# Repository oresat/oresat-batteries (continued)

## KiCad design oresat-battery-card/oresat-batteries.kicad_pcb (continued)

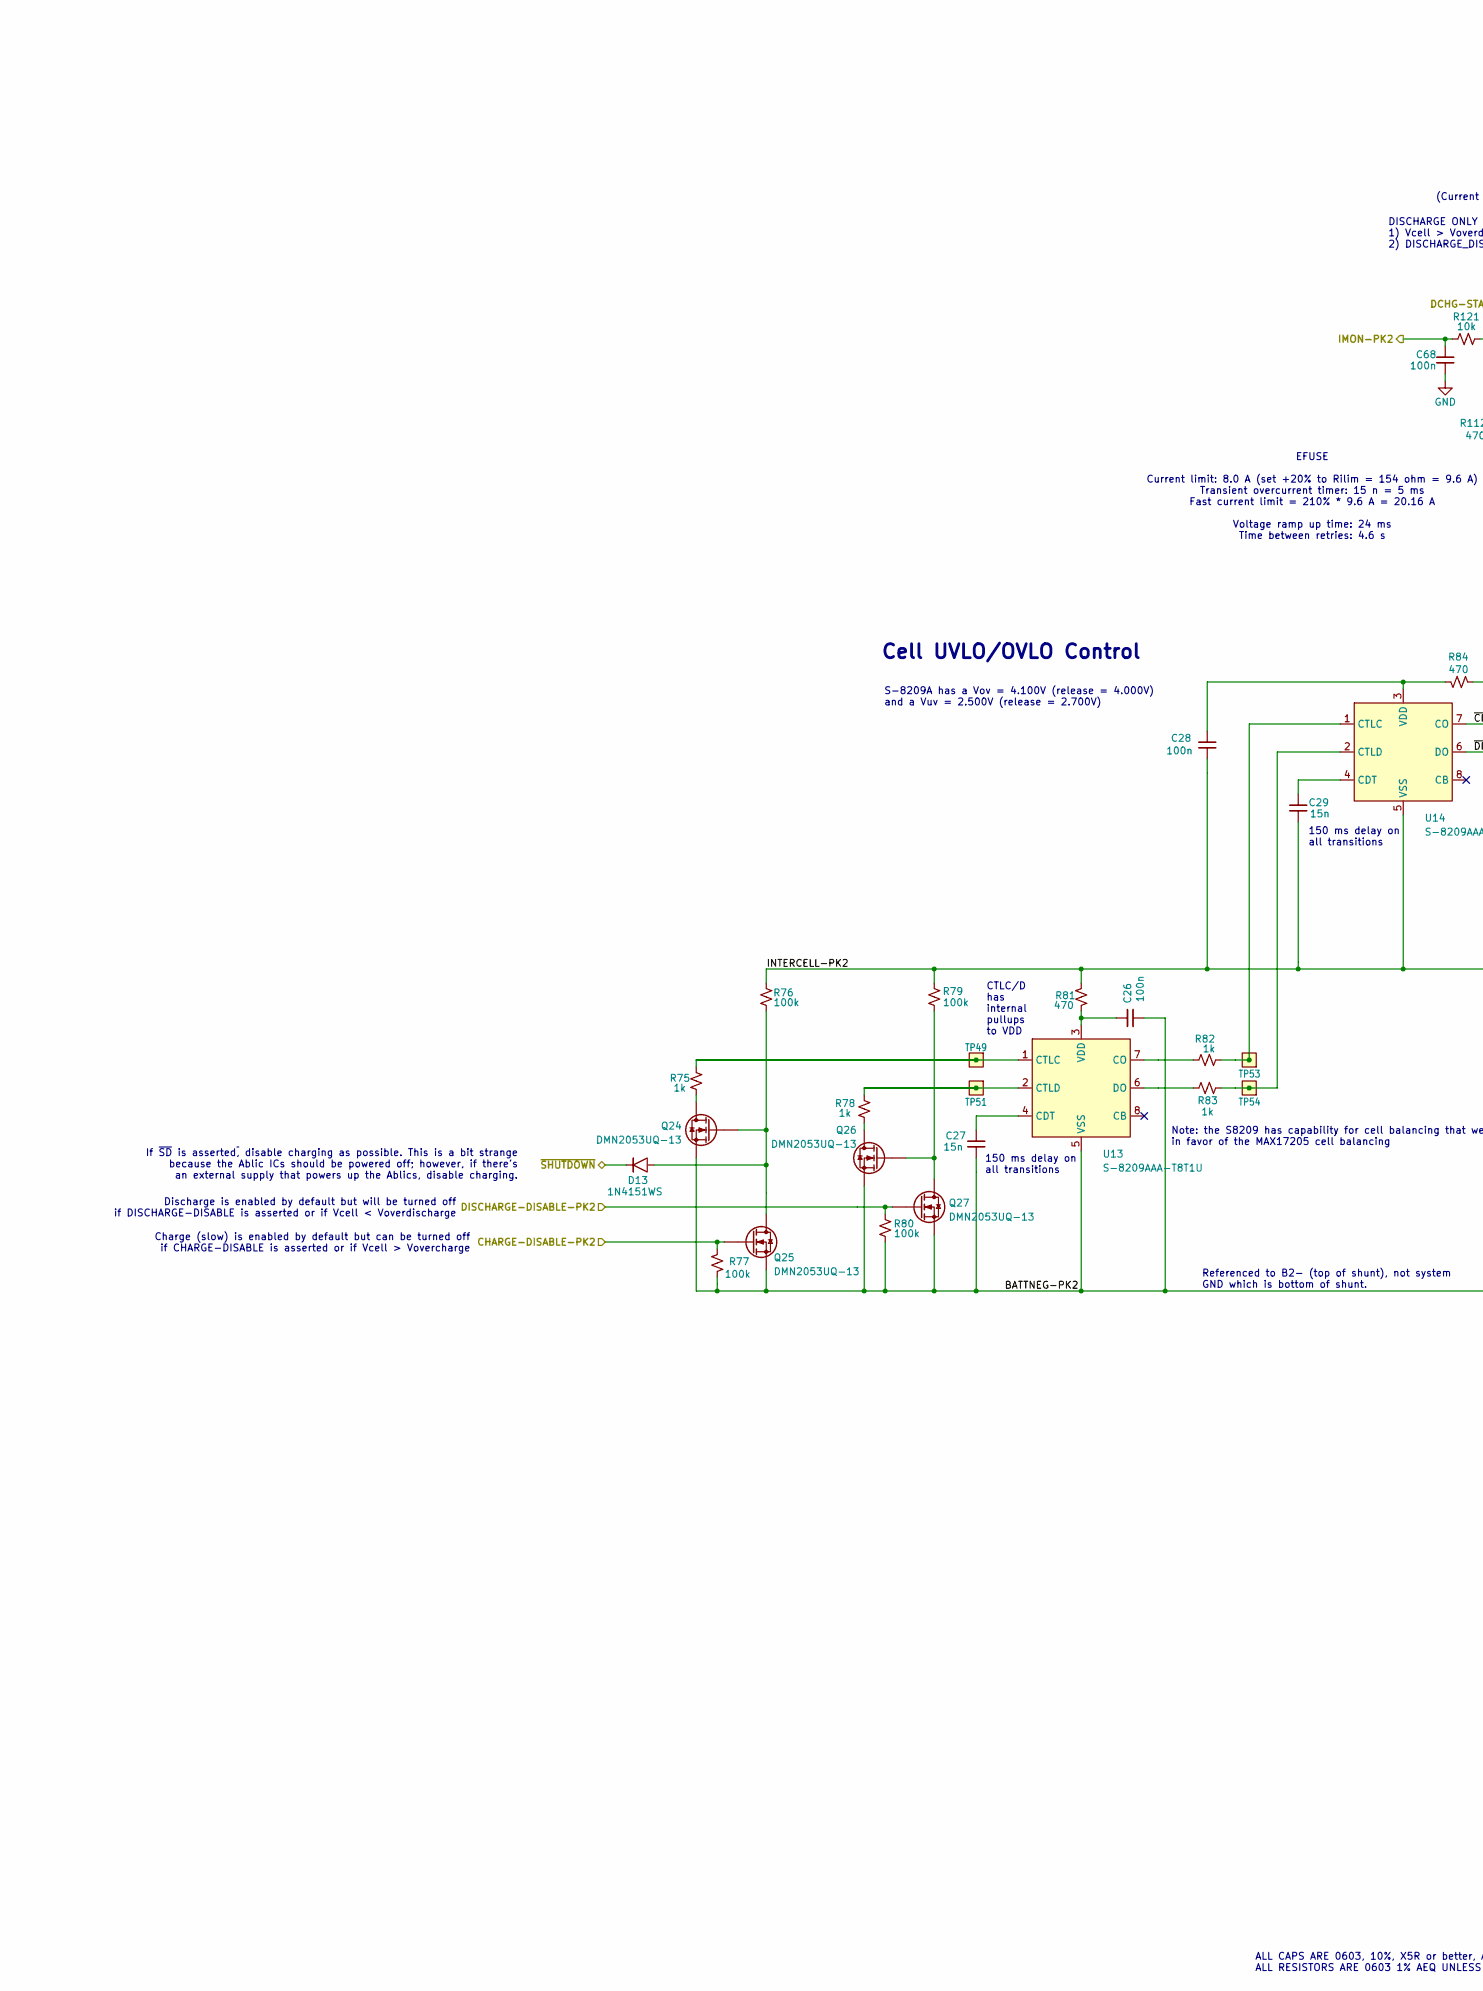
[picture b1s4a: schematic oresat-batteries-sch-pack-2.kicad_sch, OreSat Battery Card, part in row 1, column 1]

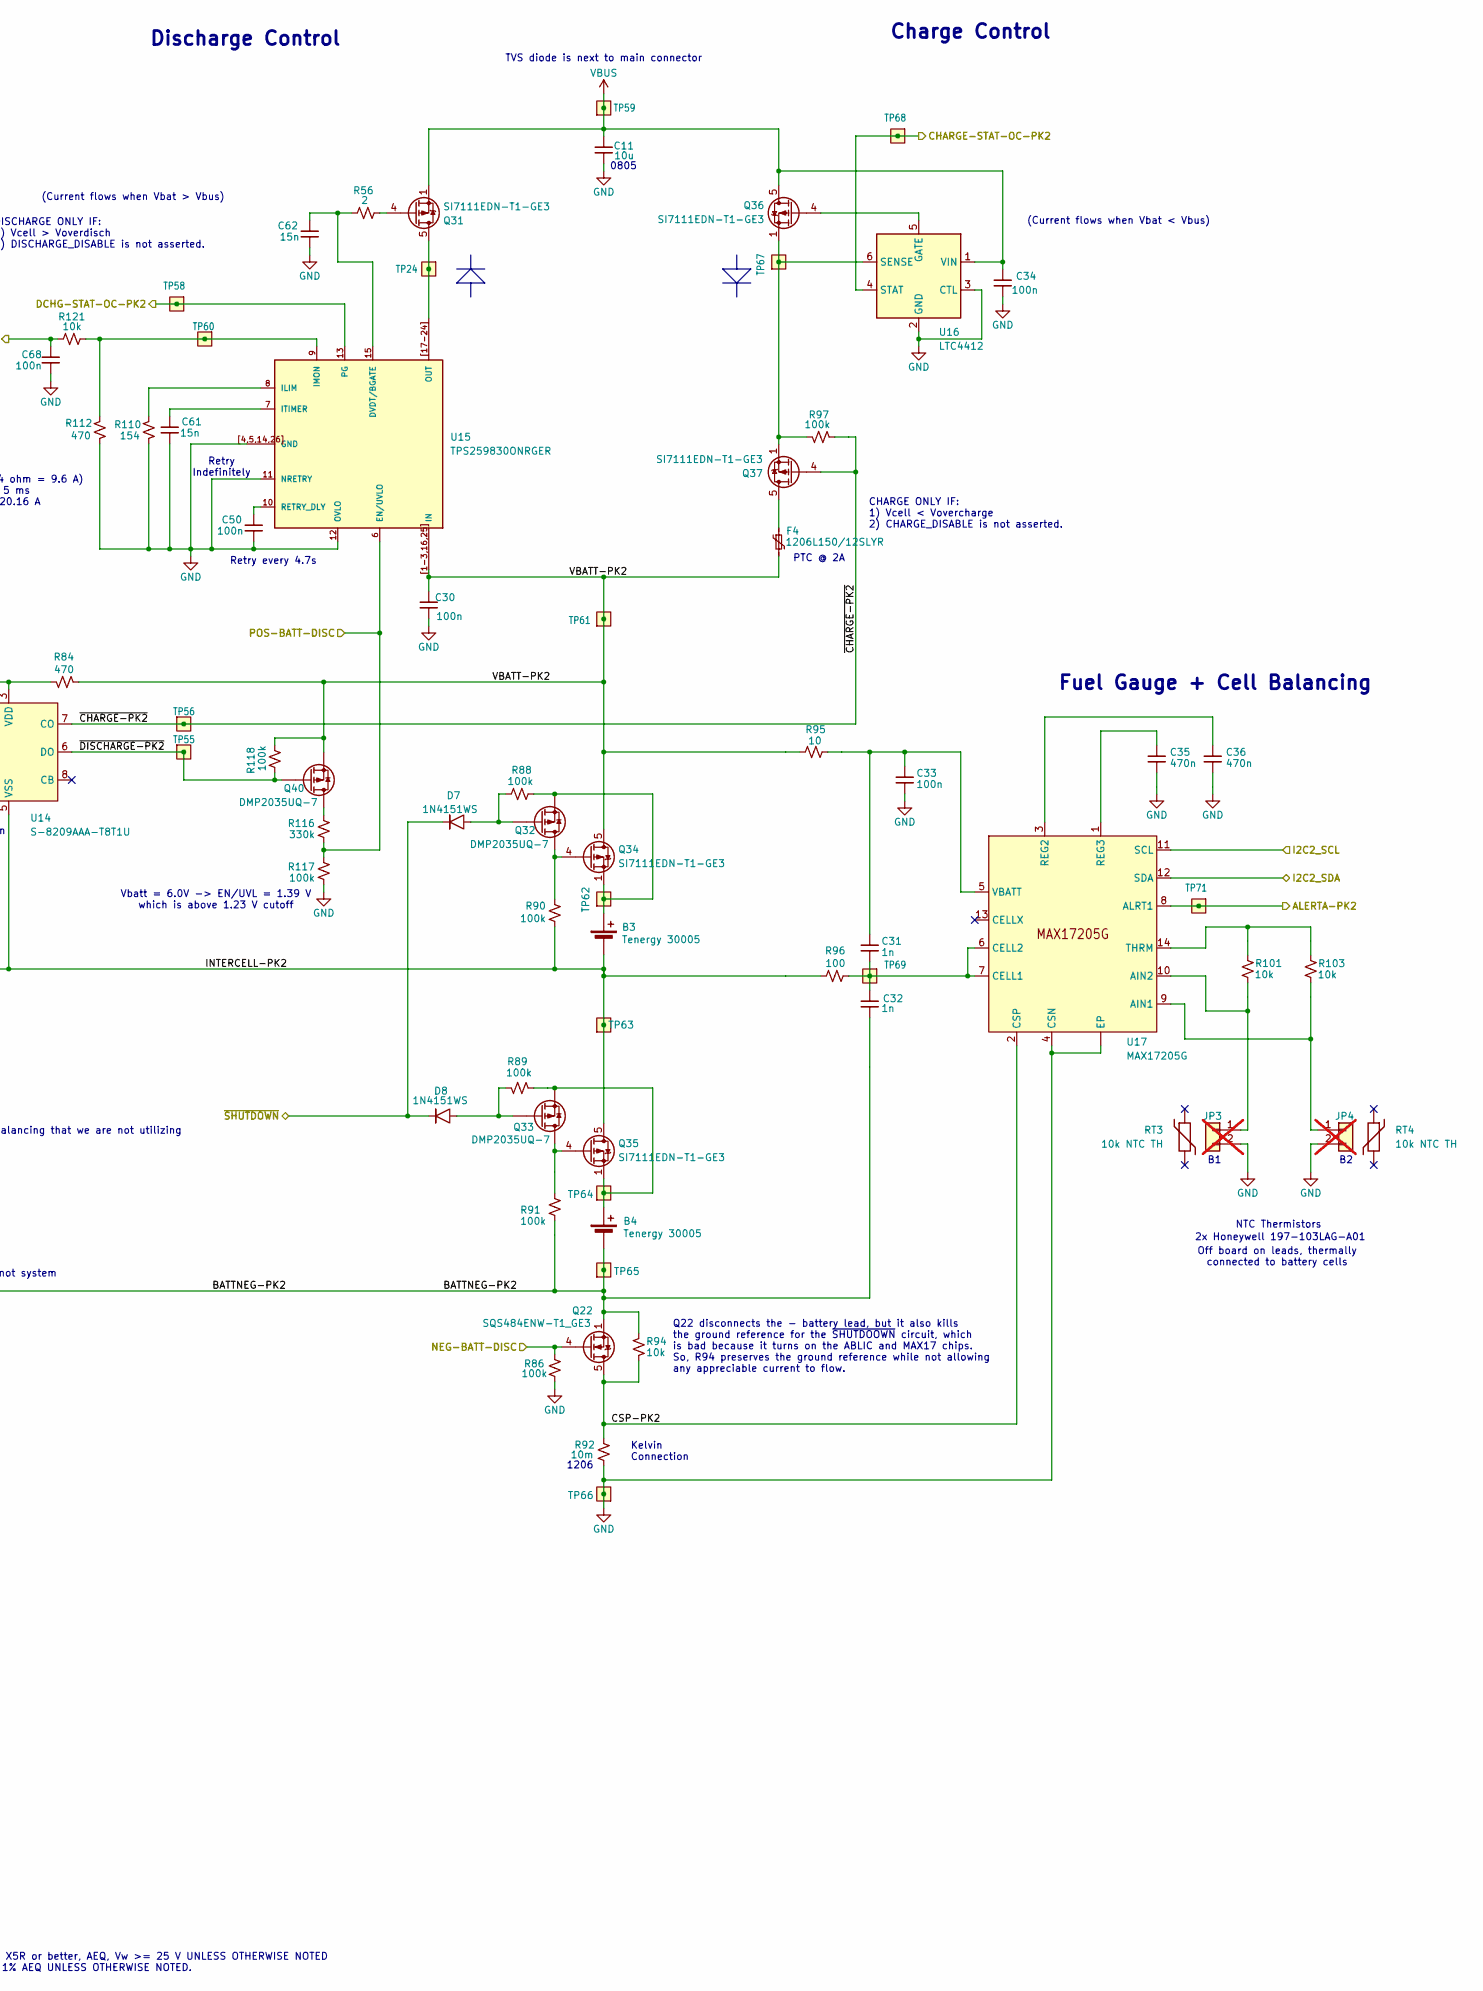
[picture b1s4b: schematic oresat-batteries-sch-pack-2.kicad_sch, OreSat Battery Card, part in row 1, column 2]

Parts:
B3, B4: Tenergy 30005; 18650; MPN MH48285
C11: 10u; 0805-C-NOSILK; MPN GRT21BC71E106KE13K
C26, C28, C30, C33, C34, C50, C68: 100n; 0603-C-NOSILK; MPN C0603C104K5RACAUTO
C27, C29, C61, C62: 15n; 0603-C-NOSILK; MPN C0603C153K5RACAUTO
C31, C32: 1n; 0603-C-NOSILK; MPN C0603C102J5RACAUTO
C35, C36: 470n; 0603-C-NOSILK; MPN C0603C474K3RACAUTO
D7, D8, D13: 1N4151WS; D_SOD-323; MPN 1N4151WS-E3-08
F4: 1206L150/12SLYR; 1206-C; MPN F5765CT-ND
JP3, JP4: PINHD-1X2; PinHeader_1x02_P2.54mm_Vertical; MPN N/A; not fitted
Q22: SQS484ENW-T1_GE3; Vishay_PowerPAK_1212-8_Single; MPN SQS484ENW-T1_GE3
Q24, Q25, Q26, Q27: DMN2053UQ-13; SOT-23; MPN DMN2053UQ-13
Q31, Q34, Q35, Q36, Q37: SI7111EDN-T1-GE3; Vishay_PowerPAK_1212-8_Single; MPN SI7111EDN-T1-GE3
Q32, Q33, Q40: DMP2035UQ-7; SOT-23; MPN DMP2035UQ-7
R56: 2; 0603-C-NOSILK; MPN RMCF0603FT2R00
R75, R78, R82, R83: 1k; 0603-C-NOSILK; MPN RMCF0603FT1K00
R76, R77, R79, R80, R86, R88, R89, R90, R91, R97, R117, R118: 100k; 0603-C-NOSILK; MPN RMCF0603FT100K
R81, R84, R112: 470; 0603-C-NOSILK; MPN RMCF0603FT470R
R92: 10m; 1206-C; MPN WSLP1206R0100FEA
R94, R101, R103, R121: 10k; 0603-C-NOSILK; MPN RMCF0603FT10K0
R95: 10; 0603-C-NOSILK; MPN RMCF0603FT10R0
R96: 100; 0603-C-NOSILK; MPN RMCF0603FT100R
R110: 154; 0603-C-NOSILK; MPN RMCF0603FT154R
R116: 330k; 0603-C-NOSILK; MPN RMCF0603FT330K
RT3, RT4: 10k NTC TH; MPN 197-103LAG-A01
TP24, TP49, TP51, TP53, TP54, TP55, TP56, TP58, TP59, TP60, TP61, TP62, TP63, TP64, TP65, TP66, TP67, TP68, TP69, TP71: TEST-POINT-LARGE-SQUARE; TestPoint-0.75mm-th
U13, U14: S-8209AAA-T8T1U; TSSOP-8_4.4x3mm_P0.65mm; MPN S-8209AAA-T8T1U
U15: TPS259830ONRGER; U-TPS259830LNRGER; MPN TPS259830ONRGER
U16: LTC4412; TSOT-23-6; MPN LTC4412ES6#PBF
U17: MAX17205G; TDFN-14-1EP_3x3mm_P0.4mm_EP1.78x2.35mm_ThermalVias; MPN MAX17205G

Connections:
/Battery Pack 2 (TOP)/ALERTA-PK2: TP71.1 (1_1), U17.8 (ALRT1); also elsewhere on the board
/Battery Pack 2 (TOP)/BATTNEG-PK2: B4.2 (-), C26.2, C27.2, C32.2, Q22.1 (S), Q22.2 (S), Q22.3 (S), Q24.2 (S), Q25.2 (S), Q26.2 (S), Q27.2 (S), R77.1, R80.1, R91.2, R94.2, TP65.1 (1_1), U13.5 (VSS)
/Battery Pack 2 (TOP)/CHARGE-DISABLE-PK2: Q25.1 (G), R77.2; also elsewhere on the board
/Battery Pack 2 (TOP)/CHARGE-STAT-OC-PK2: TP68.1 (1_1), U16.4 (STAT); also elsewhere on the board
/Battery Pack 2 (TOP)/CSP-PK2: Q22.5 (D), R92.1, R94.1, U17.2 (CSP)
/Battery Pack 2 (TOP)/DCHG-STAT-OC-PK2: TP58.1 (1_1), U15.13 (PG); also elsewhere on the board
/Battery Pack 2 (TOP)/DISCHARGE-DISABLE-PK2: Q27.1 (G), R80.2; also elsewhere on the board
/Battery Pack 2 (TOP)/I2C2_SCL: U17.11 (SCL); also elsewhere on the board
/Battery Pack 2 (TOP)/I2C2_SDA: U17.12 (SDA); also elsewhere on the board
/Battery Pack 2 (TOP)/IMON-PK2: C68.1, R121.2; also elsewhere on the board
/Battery Pack 2 (TOP)/INTERCELL-PK2: B3.2 (-), C28.2, C29.2, Q35.5 (D), R76.2, R79.1, R81.2, R90.2, R96.1, TP63.1 (1_1), U14.5 (VSS)
/Battery Pack 2 (TOP)/VBATT-PK2: C30.1, F4.2, Q34.5 (D), Q40.2 (S), R84.2, R95.2, R118.2, TP61.1 (1_1), U15.1 (IN), U15.2 (IN), U15.3 (IN), U15.16 (IN), U15.25 (IN), U15.[1-3,16,25] (IN)
/Battery Pack 2 (TOP)/~CHARGE-PK2: Q37.4 (G), R97.2, TP56.1 (1_1), U14.7 (CO)
/Battery Pack 2 (TOP)/~DISCHARGE-PK2: Q40.1 (G), R118.1, TP55.1 (1_1), U14.6 (DO)
/INH-NEG-BATT_DISC: Q22.4 (G), R86.1; also elsewhere on the board
/INH-POS-BATT-DISC: R116.1, R117.2, U15.6 (EN/UVLO); also elsewhere on the board
/~SHUTDOWN: D7.1, D8.1, D13.1; also elsewhere on the board
GND: C11.2, C30.2, C33.2, C34.2, C35.2, C36.2, C50.2, C61.2, C62.2, C68.2, JP3.2, JP4.2, R86.2, R92.2, R110.2, R112.2, R117.1, TP66.1 (1_1), U15.4 (GND), U15.5 (GND), U15.11 (NRETRY), U15.12 (OVLO), U15.14 (GND), U15.26 (GND), U15.[4,5,14,26] (GND), U16.2 (GND), U16.3 (CTL), U17.4 (CSN), U17.15 (EP); also elsewhere on the board
unnamed: B3.1 (+), Q32.2 (S), Q34.1 (S), Q34.2 (S), Q34.3 (S), R88.2, TP62.1 (1_1)
unnamed: B4.1 (+), Q33.2 (S), Q35.1 (S), Q35.2 (S), Q35.3 (S), R89.1, TP64.1 (1_1)
unnamed: JP3.1, R101.1, U17.10 (AIN2)
unnamed: JP4.1, R103.1, U17.9 (AIN1)
unnamed: Q24.3 (D), R75.1
unnamed: D13.2, Q24.1 (G), Q25.3 (D), R76.1
unnamed: Q26.3 (D), R78.1
unnamed: Q26.1 (G), Q27.3 (D), R79.2
unnamed: Q31.5 (D), TP24.1 (1_1), U15.17 (OUT), U15.18 (OUT), U15.19 (OUT), U15.20 (OUT), U15.21 (OUT), U15.22 (OUT), U15.23 (OUT), U15.24 (OUT), U15.[17-24] (OUT)
unnamed: Q31.4 (G), R56.2
unnamed: Q32.3 (D), Q34.4 (G), R90.1
unnamed: D7.2, Q32.1 (G), R88.1
unnamed: Q33.3 (D), Q35.4 (G), R91.1
unnamed: D8.2, Q33.1 (G), R89.2
unnamed: Q36.4 (G), U16.5 (GATE)
unnamed: F4.1, Q37.5 (D)
unnamed: Q40.3 (D), R116.2
unnamed: C27.1, U13.4 (CDT)
unnamed: R82.1, U13.7 (CO)
unnamed: R75.2, TP49.1 (1_1), U13.1 (CTLC)
unnamed: R78.2, TP51.1 (1_1), U13.2 (CTLD)
unnamed: R83.1, U13.6 (DO)
unnamed: C26.1, R81.1, U13.3 (VDD)
unnamed: C29.1, U14.4 (CDT)
unnamed: R82.2, TP53.1 (1_1), U14.1 (CTLC)
unnamed: R83.2, TP54.1 (1_1), U14.2 (CTLD)
unnamed: C28.1, R84.1, U14.3 (VDD)
unnamed: C62.1, R56.1, U15.15 (DVDT/BGATE)
unnamed: R110.1, U15.8 (ILIM)
unnamed: R112.1, R121.1, TP60.1 (1_1), U15.9 (IMON)
unnamed: C61.1, U15.7 (ITIMER)
unnamed: C50.1, U15.10 (RETRY_DLY)
unnamed: Q36.1 (S), Q36.2 (S), Q36.3 (S), Q37.1 (S), Q37.2 (S), Q37.3 (S), R97.1, TP67.1 (1_1), U16.6 (SENSE)
unnamed: C31.2, C32.1, R96.2, TP69.1 (1_1), U17.6 (CELL2), U17.7 (CELL1)
unnamed: C36.1, U17.3 (REG2)
unnamed: C35.1, U17.1 (REG3)
unnamed: R101.2, R103.2, U17.14 (THRM)
unnamed: C31.1, C33.1, R95.1, U17.5 (VBATT)
VBUS: C11.1, C34.1, Q31.1 (S), Q31.2 (S), Q31.3 (S), Q36.5 (D), TP59.1 (1_1), U16.1 (VIN); also elsewhere on the board

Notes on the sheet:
(Current flows when Vbat < Vbus)
Charge (slow) is enabled by default but can be turned off if CHARGE-DISABLE is asserted or if Vcell > Vovercharge
CTLC/D has internal pullups to VDD
ALL CAPS ARE 0603, 10%, X5R or better, AEQ, Vw >= 25 V UNLESS OTHERWISE NOTED ALL RESISTORS ARE 0603 1% AEQ UNLESS OTHERWISE NOTED.
PTC @ 2A
Kelvin Connection
NTC Thermistors
S-8209A has a Vov = 4.100V (release = 4.000V) and a Vuv = 2.500V (release = 2.700V)
0805
150 ms delay on all transitions
1206
Discharge is enabled by default but will be turned off if DISCHARGE-DISABLE is asserted or if Vcell < Voverdischarge
Q22 disconnects the - battery lead, but it also kills the ground reference for the ~{SHUTDOOWN} circuit, which is bad because it turns on the ABLIC and MAX17 chips. So, R94 preserves the ground reference while not allowing any appreciable current to flow.
Fuel Gauge + Cell Balancing
TVS diode is next to main connector
EFUSE Current limit: 8.0 A (set +20% to Rilim = 154 ohm = 9.6 A) Transient overcurrent timer: 15 n = 5 ms Fast current limit = 210% * 9.6 A = 20.16 A Voltage ramp up time: 24 ms Time between retries: 4.6 s
Off board on leads, thermally connected to battery cells
If ~{SD} is asserted~{,} disable charging as possible. This is a bit strange because the Ablic ICs should be powered off; however, if there's an external supply that powers up the Ablics, disable charging.
Cell UVLO/OVLO Control
CHARGE ONLY IF: 1) Vcell < Vovercharge 2) CHARGE_DISABLE is not asserted.
Vbatt = 6.0V -> EN/UVL = 1.39 V which is above 1.23 V cutoff
DISCHARGE ONLY IF: 1) Vcell > Voverdisch 2) DISCHARGE_DISABLE is not asserted.
Note: the S8209 has capability for cell balancing that we are not utilizing in favor of the MAX17205 cell balancing
Charge Control
(Current flows when Vbat > Vbus)
Discharge Control
Retry Indefinitely
2x Honeywell 197-103LAG-A01
Referenced to B2- (top of shunt), not system GND which is bottom of shunt.
Retry every 4.7s

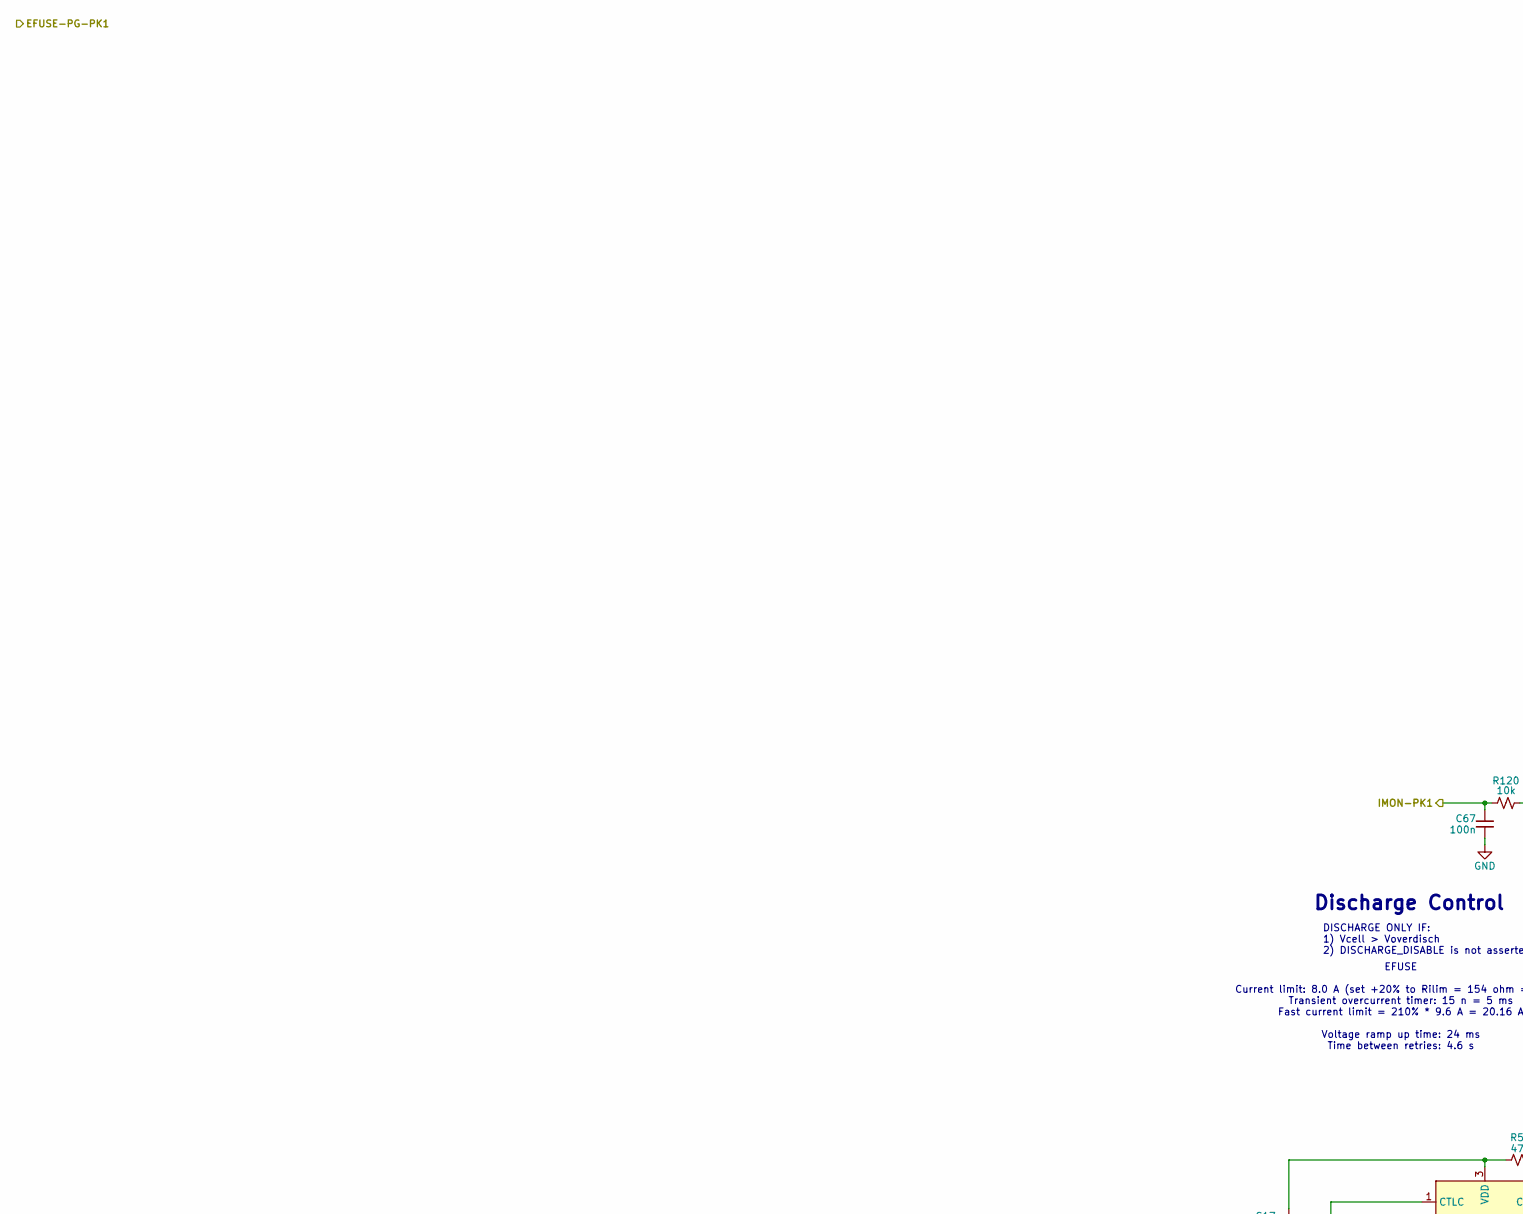
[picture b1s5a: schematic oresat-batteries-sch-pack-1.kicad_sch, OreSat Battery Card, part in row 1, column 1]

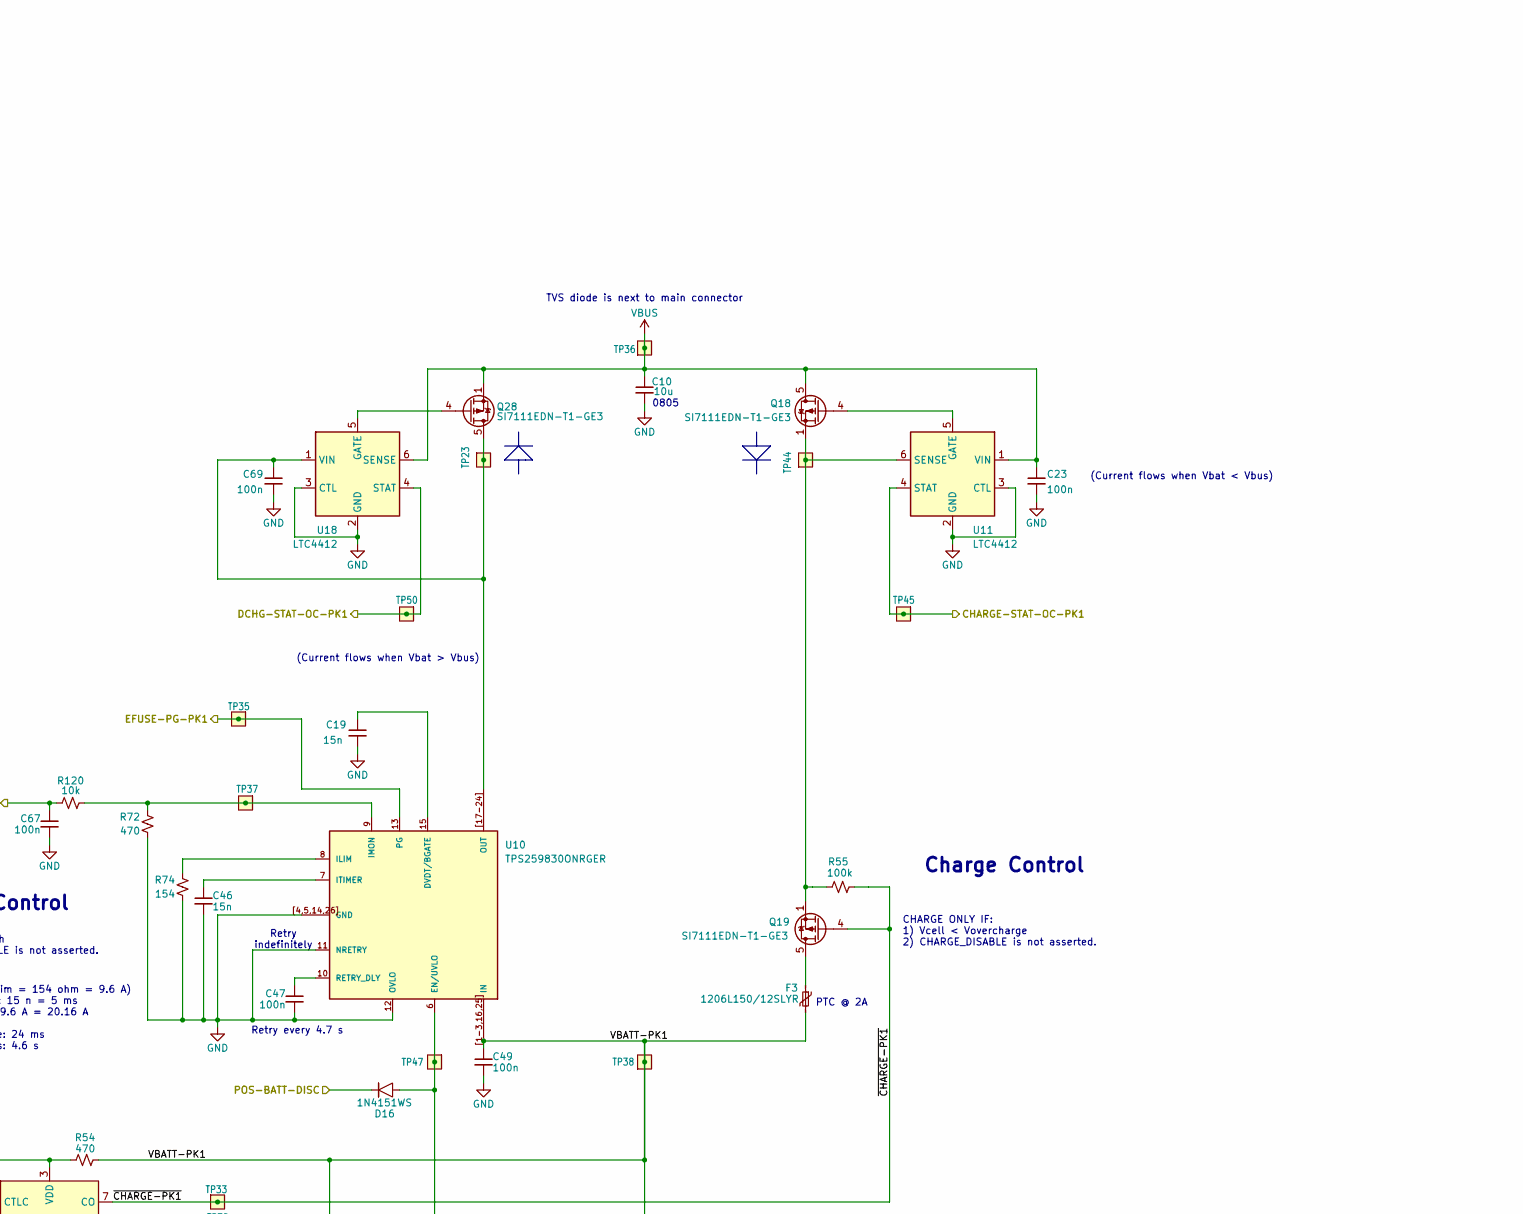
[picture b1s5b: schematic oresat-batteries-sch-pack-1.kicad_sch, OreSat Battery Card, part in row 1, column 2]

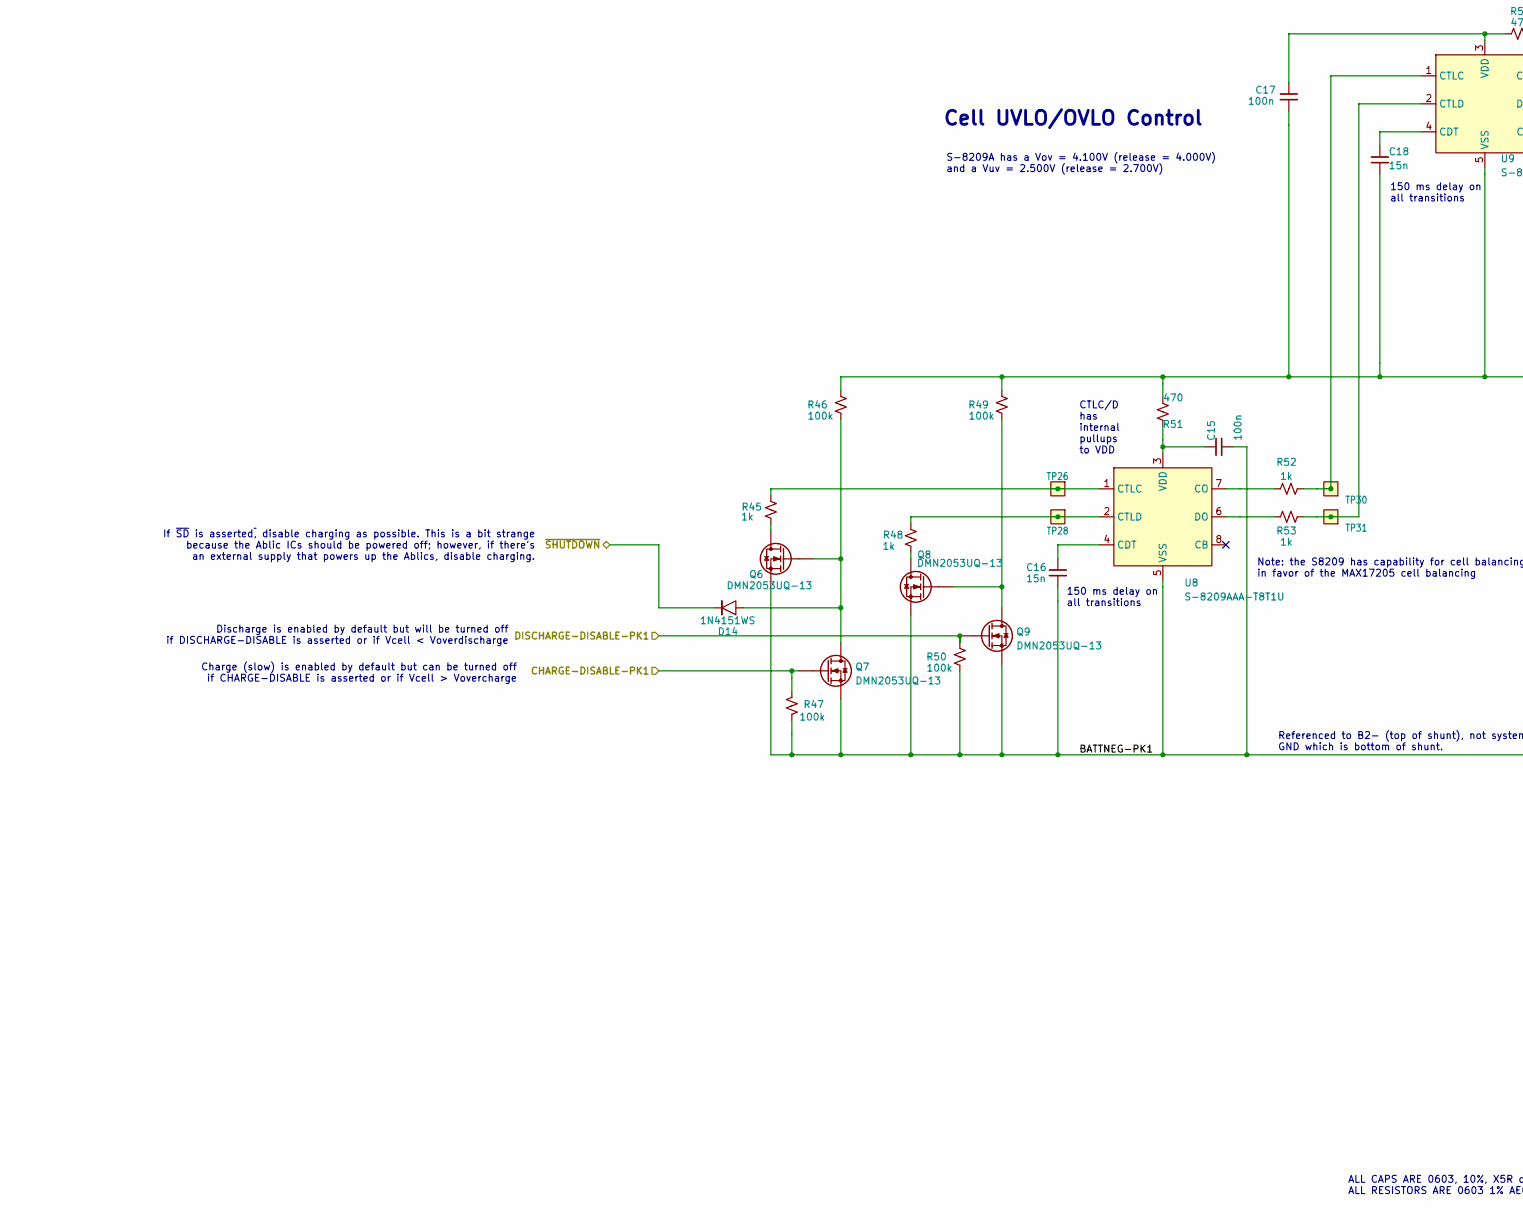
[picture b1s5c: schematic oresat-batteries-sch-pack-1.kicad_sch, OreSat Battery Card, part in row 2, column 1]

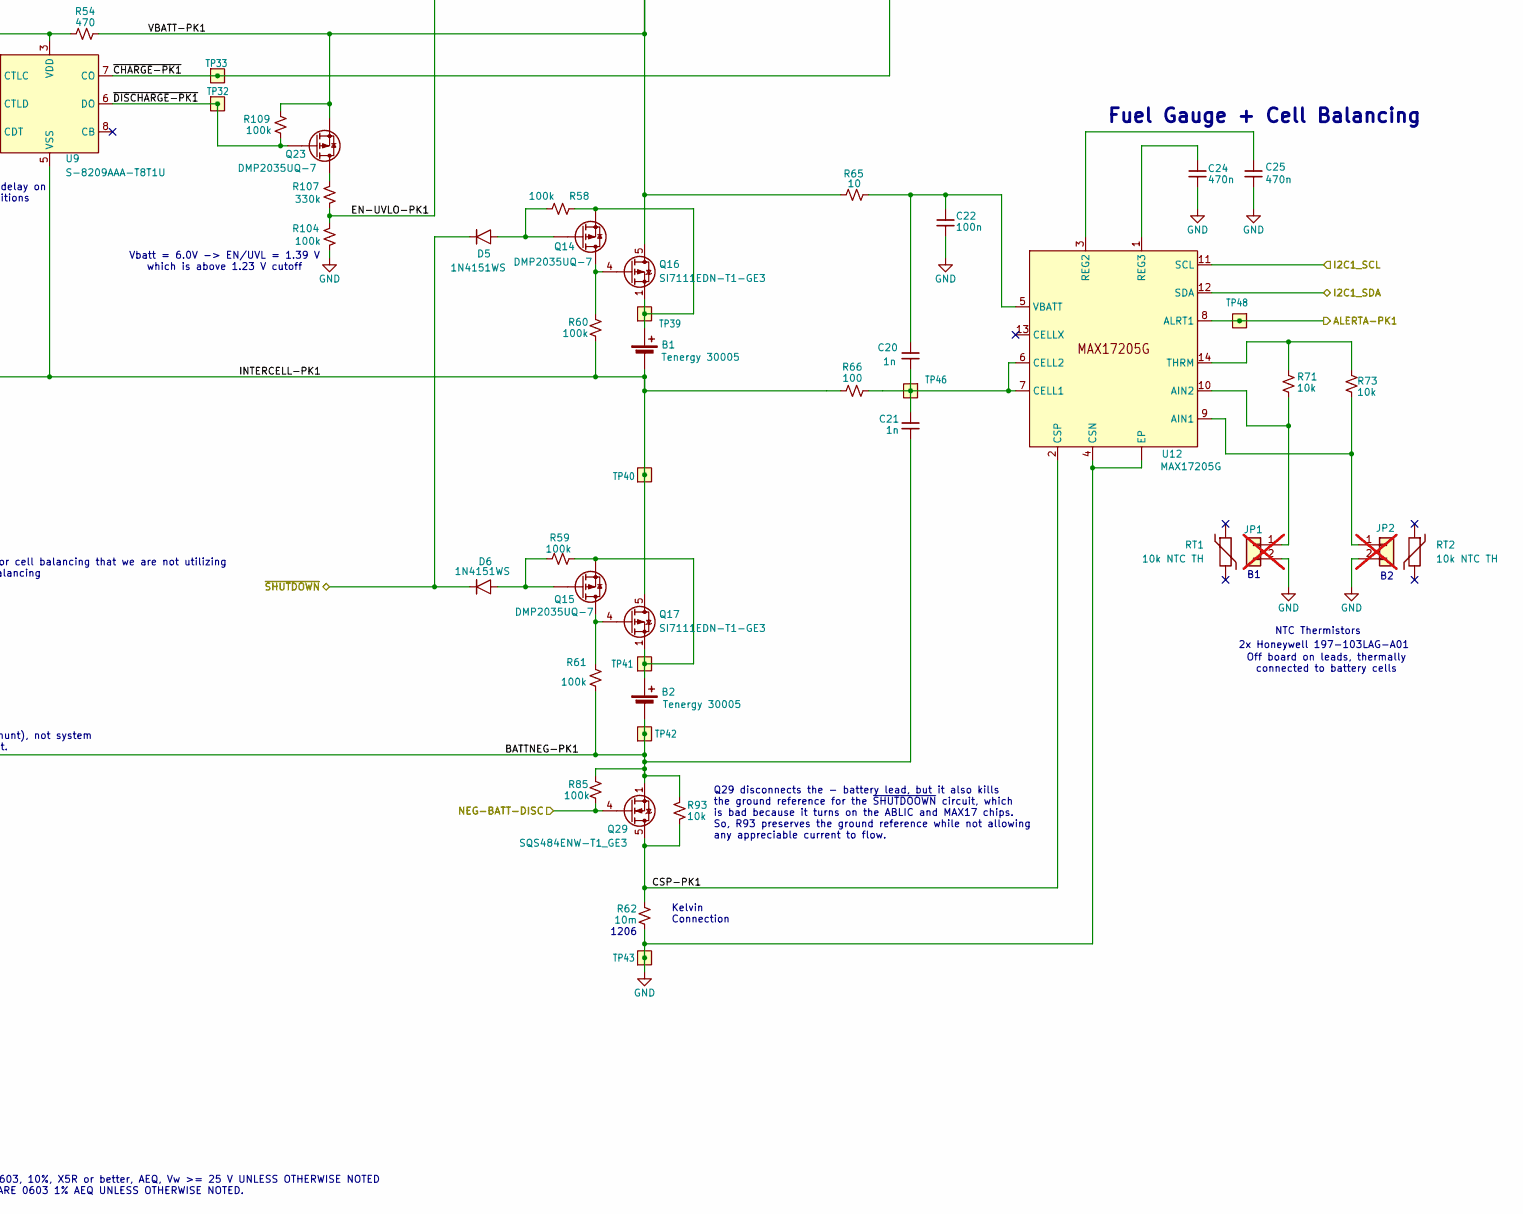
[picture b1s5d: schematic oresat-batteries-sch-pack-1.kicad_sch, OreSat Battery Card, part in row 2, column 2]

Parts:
B1, B2: Tenergy 30005; 18650; MPN MH48285
C10: 10u; 0805-C-NOSILK; MPN GRT21BC71E106KE13K
C15, C17, C22, C23, C47, C49, C67, C69: 100n; 0603-C-NOSILK; MPN C0603C104K5RACAUTO
C16, C18, C19, C46: 15n; 0603-C-NOSILK; MPN C0603C153K5RACAUTO
C20, C21: 1n; 0603-C-NOSILK; MPN C0603C102J5RACAUTO
C24, C25: 470n; 0603-C-NOSILK; MPN C0603C474K3RACAUTO
D5, D6, D14, D16: 1N4151WS; D_SOD-323; MPN 1N4151WS-E3-08
F3: 1206L150/12SLYR; 1206-C; MPN F5765CT-ND
JP1, JP2: PINHD-1X2; PinHeader_1x02_P2.54mm_Vertical; MPN N/A; not fitted
Q6, Q7, Q8, Q9: DMN2053UQ-13; SOT-23; MPN DMN2053UQ-13
Q14, Q15, Q23: DMP2035UQ-7; SOT-23; MPN DMP2035UQ-7
Q16, Q17, Q18, Q19, Q28: SI7111EDN-T1-GE3; Vishay_PowerPAK_1212-8_Single; MPN SI7111EDN-T1-GE3
Q29: SQS484ENW-T1_GE3; Vishay_PowerPAK_1212-8_Single; MPN SQS484ENW-T1_GE3
R45, R48, R52, R53: 1k; 0603-C-NOSILK; MPN RMCF0603FT1K00
R46, R47, R49, R50, R55, R58, R59, R60, R61, R85, R104, R109: 100k; 0603-C-NOSILK; MPN RMCF0603FT100K
R51, R54, R72: 470; 0603-C-NOSILK; MPN RMCF0603FT470R
R62: 10m; 1206-C; MPN WSLP1206R0100FEA
R65: 10; 0603-C-NOSILK; MPN RMCF0603FT10R0
R66: 100; 0603-C-NOSILK; MPN RMCF0603FT100R
R71, R73, R93, R120: 10k; 0603-C-NOSILK; MPN RMCF0603FT10K0
R74: 154; 0603-C-NOSILK; MPN RMCF0603FT154R
R107: 330k; 0603-C-NOSILK; MPN RMCF0603FT330K
RT1, RT2: 10k NTC TH; MPN 197-103LAG-A01
TP23, TP26, TP28, TP30, TP31, TP32, TP33, TP35, TP36, TP37, TP38, TP39, TP40, TP41, TP42, TP43, TP44, TP45, TP46, TP47, TP48, TP50: TEST-POINT-LARGE-SQUARE; TestPoint-0.75mm-th
U8, U9: S-8209AAA-T8T1U; TSSOP-8_4.4x3mm_P0.65mm; MPN S-8209AAA-T8T1U
U10: TPS259830ONRGER; U-TPS259830LNRGER; MPN TPS259830ONRGER
U11, U18: LTC4412; TSOT-23-6; MPN LTC4412ES6#PBF
U12: MAX17205G; TDFN-14-1EP_3x3mm_P0.4mm_EP1.78x2.35mm_ThermalVias; MPN MAX17205G

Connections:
/Battery Pack 1 (BOTTOM)/ALERTA-PK1: TP48.1 (1_1), U12.8 (ALRT1); also elsewhere on the board
/Battery Pack 1 (BOTTOM)/BATTNEG-PK1: B2.2 (-), C15.2, C16.2, C21.2, Q6.2 (S), Q7.2 (S), Q8.2 (S), Q9.2 (S), Q29.1 (S), Q29.2 (S), Q29.3 (S), R47.1, R50.1, R61.2, R85.2, R93.2, TP42.1 (1_1), U8.5 (VSS)
/Battery Pack 1 (BOTTOM)/CHARGE-DISABLE-PK1: Q7.1 (G), R47.2; also elsewhere on the board
/Battery Pack 1 (BOTTOM)/CHARGE-STAT-OC-PK1: TP45.1 (1_1), U11.4 (STAT); also elsewhere on the board
/Battery Pack 1 (BOTTOM)/CSP-PK1: Q29.5 (D), R62.1, R93.1, U12.2 (CSP)
/Battery Pack 1 (BOTTOM)/DCHG-STAT-OC-PK1: TP50.1 (1_1), U18.4 (STAT); also elsewhere on the board
/Battery Pack 1 (BOTTOM)/DISCHARGE-DISABLE-PK1: Q9.1 (G), R50.2; also elsewhere on the board
/Battery Pack 1 (BOTTOM)/EFUSE-PG-PK1: TP35.1 (1_1), U10.13 (PG); also elsewhere on the board
/Battery Pack 1 (BOTTOM)/EN-UVLO-PK1: D16.2, R104.2, R107.1, TP47.1 (1_1), U10.6 (EN/UVLO)
/Battery Pack 1 (BOTTOM)/I2C1_SCL: U12.11 (SCL); also elsewhere on the board
/Battery Pack 1 (BOTTOM)/I2C1_SDA: U12.12 (SDA); also elsewhere on the board
/Battery Pack 1 (BOTTOM)/IMON-PK1: C67.1, R120.2; also elsewhere on the board
/Battery Pack 1 (BOTTOM)/INTERCELL-PK1: B1.2 (-), C17.2, C18.2, Q17.5 (D), R46.2, R49.1, R51.2, R60.2, R66.1, TP40.1 (1_1), U9.5 (VSS)
/Battery Pack 1 (BOTTOM)/VBATT-PK1: C49.1, F3.2, Q16.5 (D), Q23.2 (S), R54.2, R65.2, R109.1, TP38.1 (1_1), U10.1 (IN), U10.2 (IN), U10.3 (IN), U10.16 (IN), U10.25 (IN), U10.[1-3,16,25] (IN)
/Battery Pack 1 (BOTTOM)/~CHARGE-PK1: Q19.4 (G), R55.1, TP33.1 (1_1), U9.7 (CO)
/Battery Pack 1 (BOTTOM)/~DISCHARGE-PK1: Q23.1 (G), R109.2, TP32.1 (1_1), U9.6 (DO)
/INH-NEG-BATT_DISC: Q29.4 (G), R85.1; also elsewhere on the board
/INH-POS-BATT-DISC: D16.1; also elsewhere on the board
/~SHUTDOWN: D5.1, D6.1, D14.1; also elsewhere on the board
GND: C10.2, C19.2, C22.2, C23.2, C24.2, C25.2, C46.2, C47.2, C49.2, C67.2, C69.2, JP1.2, JP2.2, R62.2, R72.2, R74.2, R104.1, TP43.1 (1_1), U10.4 (GND), U10.5 (GND), U10.11 (NRETRY), U10.12 (OVLO), U10.14 (GND), U10.26 (GND), U10.[4,5,14,26] (GND), U11.2 (GND), U11.3 (CTL), U12.4 (CSN), U12.15 (EP), U18.2 (GND), U18.3 (CTL); also elsewhere on the board
unnamed: B1.1 (+), Q14.2 (S), Q16.1 (S), Q16.2 (S), Q16.3 (S), R58.2, TP39.1 (1_1)
unnamed: B2.1 (+), Q15.2 (S), Q17.1 (S), Q17.2 (S), Q17.3 (S), R59.1, TP41.1 (1_1)
unnamed: JP1.1, R71.1, U12.10 (AIN2)
unnamed: JP2.1, R73.1, U12.9 (AIN1)
unnamed: Q6.3 (D), R45.1
unnamed: D14.2, Q6.1 (G), Q7.3 (D), R46.1
unnamed: Q8.3 (D), R48.1
unnamed: Q8.1 (G), Q9.3 (D), R49.2
unnamed: Q14.3 (D), Q16.4 (G), R60.1
unnamed: D5.2, Q14.1 (G), R58.1
unnamed: Q15.3 (D), Q17.4 (G), R61.1
unnamed: D6.2, Q15.1 (G), R59.2
unnamed: Q18.4 (G), U11.5 (GATE)
unnamed: F3.1, Q19.5 (D)
unnamed: Q23.3 (D), R107.2
unnamed: C69.1, Q28.5 (D), TP23.1 (1_1), U10.17 (OUT), U10.18 (OUT), U10.19 (OUT), U10.20 (OUT), U10.21 (OUT), U10.22 (OUT), U10.23 (OUT), U10.24 (OUT), U10.[17-24] (OUT), U18.1 (VIN)
unnamed: Q28.4 (G), U18.5 (GATE)
unnamed: C16.1, U8.4 (CDT)
unnamed: R52.1, U8.7 (CO)
unnamed: R45.2, TP26.1 (1_1), U8.1 (CTLC)
unnamed: R48.2, TP28.1 (1_1), U8.2 (CTLD)
unnamed: R53.1, U8.6 (DO)
unnamed: C15.1, R51.1, U8.3 (VDD)
unnamed: C18.1, U9.4 (CDT)
unnamed: R52.2, TP30.1 (1_1), U9.1 (CTLC)
unnamed: R53.2, TP31.1 (1_1), U9.2 (CTLD)
unnamed: C17.1, R54.1, U9.3 (VDD)
unnamed: C19.1, U10.15 (DVDT/BGATE)
unnamed: R74.1, U10.8 (ILIM)
unnamed: R72.1, R120.1, TP37.1 (1_1), U10.9 (IMON)
unnamed: C46.1, U10.7 (ITIMER)
unnamed: C47.1, U10.10 (RETRY_DLY)
unnamed: Q18.1 (S), Q18.2 (S), Q18.3 (S), Q19.1 (S), Q19.2 (S), Q19.3 (S), R55.2, TP44.1 (1_1), U11.6 (SENSE)
unnamed: C20.2, C21.1, R66.2, TP46.1 (1_1), U12.6 (CELL2), U12.7 (CELL1)
unnamed: C25.1, U12.3 (REG2)
unnamed: C24.1, U12.1 (REG3)
unnamed: R71.2, R73.2, U12.14 (THRM)
unnamed: C20.1, C22.1, R65.1, U12.5 (VBATT)
VBUS: C10.1, C23.1, Q18.5 (D), Q28.1 (S), Q28.2 (S), Q28.3 (S), TP36.1 (1_1), U11.1 (VIN), U18.6 (SENSE); also elsewhere on the board

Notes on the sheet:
Discharge Control
CHARGE ONLY IF: 1) Vcell < Vovercharge 2) CHARGE_DISABLE is not asserted.
150 ms delay on all transitions
CTLC/D has internal pullups to VDD
Q29 disconnects the - battery lead, but it also kills the ground reference for the ~{SHUTDOOWN} circuit, which is bad because it turns on the ABLIC and MAX17 chips. So, R93 preserves the ground reference while not allowing any appreciable current to flow.
EFUSE Current limit: 8.0 A (set +20% to Rilim = 154 ohm = 9.6 A) Transient overcurrent timer: 15 n = 5 ms Fast current limit = 210% * 9.6 A = 20.16 A Voltage ramp up time: 24 ms Time between retries: 4.6 s
PTC @ 2A
Vbatt = 6.0V -> EN/UVL = 1.39 V which is above 1.23 V cutoff
(Current flows when Vbat > Vbus)
(Current flows when Vbat < Vbus)
Discharge is enabled by default but will be turned off if DISCHARGE-DISABLE is asserted or if Vcell < Voverdischarge
NTC Thermistors
Note: the S8209 has capability for cell balancing that we are not utilizing in favor of the MAX17205 cell balancing
Fuel Gauge + Cell Balancing
Kelvin Connection
Retry every 4.7 s
Charge (slow) is enabled by default but can be turned off if CHARGE-DISABLE is asserted or if Vcell > Vovercharge
S-8209A has a Vov = 4.100V (release = 4.000V) and a Vuv = 2.500V (release = 2.700V)
Referenced to B2- (top of shunt), not system GND which is bottom of shunt.
TVS diode is next to main connector
Off board on leads, thermally connected to battery cells
If ~{SD} is asserted~{,} disable charging as possible. This is a bit strange because the Ablic ICs should be powered off; however, if there's an external supply that powers up the Ablics, disable charging.
1206
Cell UVLO/OVLO Control
2x Honeywell 197-103LAG-A01
ALL CAPS ARE 0603, 10%, X5R or better, AEQ, Vw >= 25 V UNLESS OTHERWISE NOTED ALL RESISTORS ARE 0603 1% AEQ UNLESS OTHERWISE NOTED.
Retry indefinitely
DISCHARGE ONLY IF: 1) Vcell > Voverdisch 2) DISCHARGE_DISABLE is not asserted.
Charge Control
0805
